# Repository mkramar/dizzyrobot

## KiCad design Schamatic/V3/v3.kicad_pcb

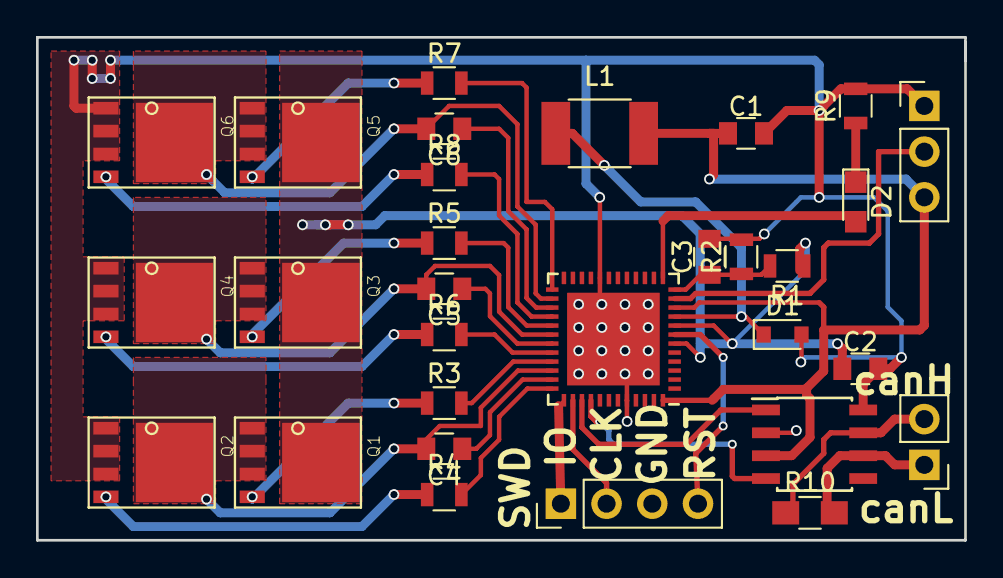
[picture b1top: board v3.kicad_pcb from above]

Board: 2 copper layers, 51.6 x 27.9 mm, 30 parts (0 on the bottom side), 33 nets.

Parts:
C1: 47uF; C_0805
C2, C3, C4, C5, C6: 1uF; C_0805
D1: D; D_0805
D2: LED; LED_0805
J1: SWD; Pin_Header_Straight_1x04_Pitch2.54mm
J2: SENSOR; Pin_Header_Straight_1x03_Pitch2.54mm
J3: CAN; Pin_Header_Straight_1x02_Pitch2.54mm
L1: 22uH; L_1812
Q1, Q2, Q3, Q4, Q5, Q6: PSMN3R3-40YS; LFPAK
R1: 47K; R_0805
R2: 10K; R_0805
R3, R4, R5, R6, R7, R8: 10; R_0805
R9: 120; R_0805
R10: 120; R_0805_HandSoldering
U1: STSPIN32F0; QFN-48-1EP_7x7mm_Pitch0.5mm
U2: L9616; SOIC-8_3.9x4.9mm_Pitch1.27mm

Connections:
+3V3: C1.1, J2.3, L1.2, U1.10, U1.48, U2.3
+12V: C2.1, Q1.5678, Q3.5678, Q5.5678, R1.1, U1.6, U1.8
BOOT1: C4.1, U1.35
BOOT2: C5.1, U1.31
BOOT3: C6.1, U1.27
CANH: J3.2, R10.1, U2.7
CANL: J3.1, R10.2, U2.6
Earth: C1.2, C2.2, C3.2, D1.2, J1.3, J2.1, Q2.1, Q2.2, Q2.3, Q4.1, Q4.2, Q4.3, Q6.1, Q6.2, Q6.3, R2.2, R9.2, U1.20, U1.44, U1.49, U2.2, U2.8
H1: R3.2, U1.33
H2: R5.2, U1.29
H3: R7.2, U1.25
L1: R4.2, U1.36
L2: R6.2, U1.32
L3: R8.2, U1.28
NRST: J1.4, U1.7
unnamed: C3.1, R1.2, R2.1, U1.12
unnamed: D1.1, L1.1, U1.9
unnamed: D2.1, R9.1
unnamed: D2.2, U1.13
unnamed: Q1.4, R3.1
unnamed: Q2.4, R4.1
unnamed: Q3.4, R5.1
unnamed: Q4.4, R6.1
unnamed: Q5.4, R7.1
unnamed: Q6.4, R8.1
O1: C4.2, Q1.1, Q1.2, Q1.3, Q2.5678, U1.34
O2: C5.2, Q3.1, Q3.2, Q3.3, Q4.5678, U1.30
O3: C6.2, Q5.1, Q5.2, Q5.3, Q6.5678, U1.26
RX: U1.40, U2.4
SENS: J2.2, U1.11
SWDCLK: J1.2, U1.38
SWDIO: J1.1, U1.37
TX: U1.39, U2.1
